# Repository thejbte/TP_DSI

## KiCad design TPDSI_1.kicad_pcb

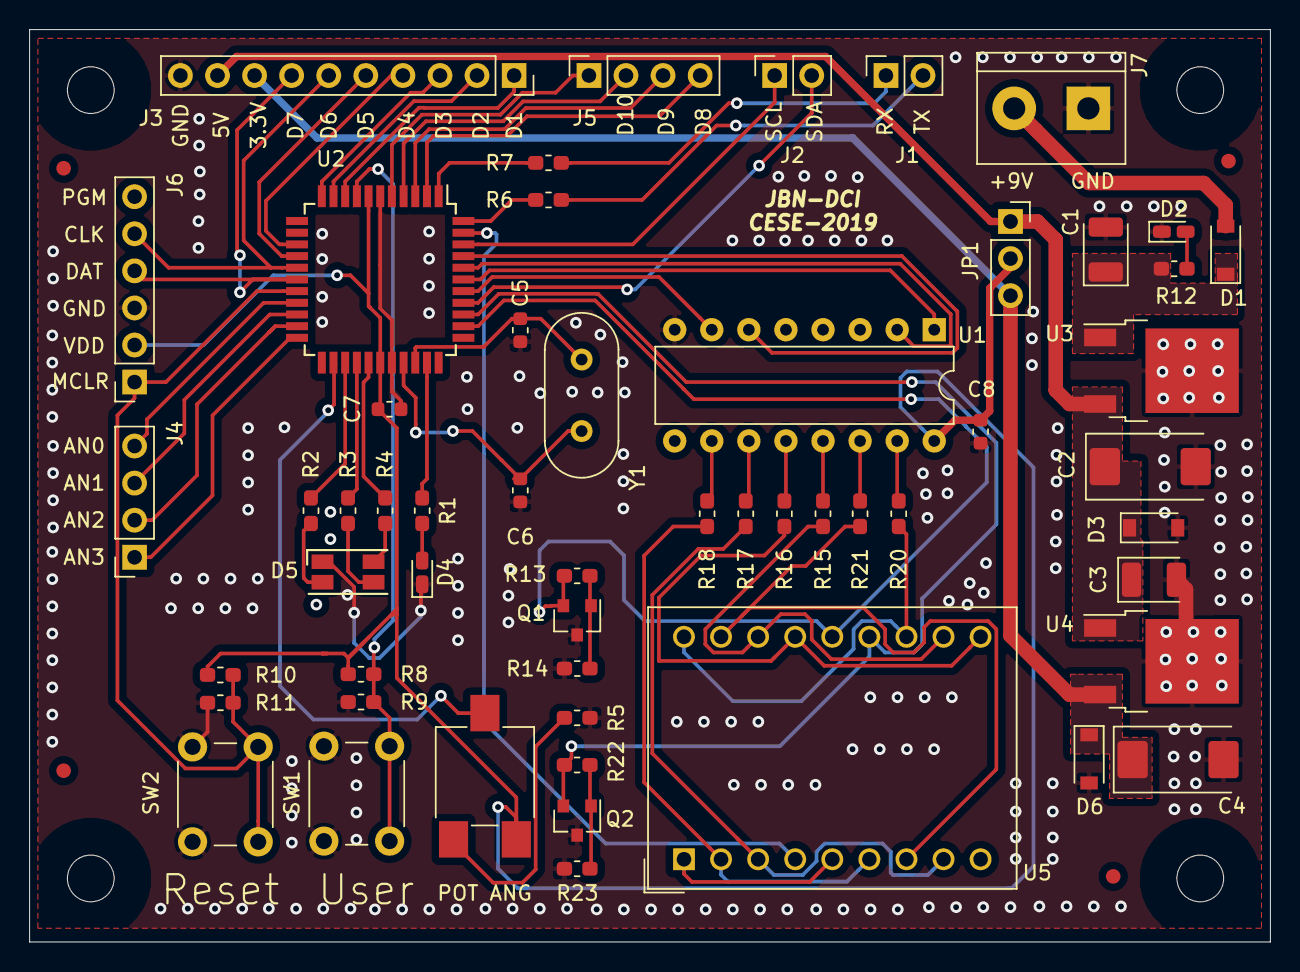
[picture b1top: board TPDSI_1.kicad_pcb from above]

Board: 2 copper layers, 85.0 x 62.5 mm, 63 parts (0 on the bottom side), 64 nets.

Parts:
C1, C3: 1uF; CP_EIA-3528-21_Kemet-B
C2: 22uF; CP_EIA-7343-20_Kemet-V
C4: 10uF; CP_EIA-7343-20_Kemet-V
C5, C6: 22pF; C_0603_1608Metric
C7, C8: 0.1uF; C_0603_1608Metric
D1: 1n4148; D_SOD-123
D2, D4: LED; LED_0603_1608Metric_Castellated
D3: D_TVS_DESD5V0S1BA-7DITR-ND; D_SOD-123
D5: LED_CRGB; LED_RGB_1210
D6: D_TVS_3V3; D_SOD-123
FID1, FID2, FID3, FID4: Fiducial; Fiducial_1mm_Mask2mm
H1, H2, H3, H4: MountingHole; MountingHole_3.2mm_M3
J1, J2: Conn_01x02_Male; PinSocket_1x02_P2.54mm_Vertical
J3: Conn_01x10_Male; PinSocket_1x10_P2.54mm_Vertical
J4, J5: Conn_01x04_Male; PinSocket_1x04_P2.54mm_Vertical
J6: Conn_01x06_Male; PinSocket_1x06_P2.54mm_Vertical
J7: Screw_Terminal_01x02; TerminalBlock_bornier-2_P5.08mm
JP1: Jumper_NC_Dual; PinSocket_1x03_P2.54mm_Vertical
Q1, Q2: Q_NPN_BCE; SOT-23
R1, R2, R3, R4, R12, R15, R16, R17, R18, R20, R21: 330; R_0603_1608Metric_Pad1.05x0.95mm_HandSolder
R5, R13, R22: 1K; R_0603_1608Metric_Pad1.05x0.95mm_HandSolder
R6, R7: 470; R_0603_1608Metric_Pad1.05x0.95mm_HandSolder
R8, R10, R14, R23: 10K; R_0603_1608Metric_Pad1.05x0.95mm_HandSolder
R9, R11: DNP-10K; R_0603_1608Metric_Pad1.05x0.95mm_HandSolder
RV1: 10K; Potentiometer_ACP_CA6-VSMD_Vertical
SW1, SW2: SW_Push; SW_PUSH_6mm_H5mm
U1: 74LS47; DIP-16_W7.62mm
U2: PIC16F1939-IPT; TQFP-44_10x10mm_P0.8mm
U3: MC7805_TO252-3(DPACK); TO-252-2
U4: TLV2217_TO252-3; TO-252-2
U5: DA56-11GWA; DA56-11CGKWA
Y1: Crystal; Crystal_HC18-U_Vertical

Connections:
+3V3: C4.1, D6.1, J3.8, JP1.3, U4.3
+5V: C2.1, C3.1, D3.1, J3.9, JP1.1, U3.3, U4.1
/9V0: D1.2, J7.2
/AN0: J4.4, U2.19
/AN1: J4.3, U2.20
/AN2: J4.2, U2.21
/AN3: J4.1, U2.22
/Display/DIG1_CA: Q1.2, R13.2, U2.35, U5.14
/Display/DIG2_CA: Q2.2, R22.2, U2.36, U5.13
/Display/DP1: U2.43, U5.4
/Display/a: R15.1, U5.11, U5.16
/Display/b: R16.1, U5.10, U5.15
/Display/c: R17.1, U5.3, U5.8
/Display/d: R18.1, U5.2, U5.6
/Display/e: U5.1, U5.5
/Display/f: R20.1, U5.12, U5.18
/Display/g: R21.1, U5.7, U5.17
/LED_B: R4.1, U2.27
/LED_G: R3.1, U2.26
/LED_OUT: R1.1, U2.32
/LED_R: R2.1, U2.25
/Microcontroller/MCLR_VPP: J6.1, R10.2, R11.1, SW2.2, U2.18
/Microcontroller/RD0: U1.7, U2.38
/Microcontroller/RD1: U1.1, U2.39
/Microcontroller/RD2: U1.2, U2.40
/Microcontroller/RD3: U1.6, U2.41
/Microcontroller/RX: J1.1, R7.2
/Microcontroller/TX: J1.2, R6.2
/Microcontroller/USER_BUTTON: R8.2, R9.1, SW1.2, U2.8
/POTENCIOMETRO: RV1.2, U2.24
/RB1: J3.1, U2.9
/RB2: J3.2, U2.10
/RB3: J3.3, U2.11
/RB4: J3.4, U2.14
/RB5: J3.5, U2.15
/RB6: J3.6, J6.5, U2.16
/RB7: J3.7, J6.4, U2.17
/RD4: J5.4, U2.2
/RD5: J5.3, U2.3
/RD6: J5.2, U2.4
/RD7: J5.1, U2.5
/SCL: J2.1, U2.42
/SDA: J2.2, U2.37
GND: C1.2, C2.2, C3.2, C4.2, C5.1, C6.1, C7.1, C8.1, D2.1, D3.2, D4.1, D5.1, D6.2, J3.10, J6.3, J7.1, Q1.3, Q2.3, R5.2, R9.2, R11.2, R14.2, R23.2, SW1.1, SW2.1, U1.8, U2.6, U2.29, U3.2, U4.2
unnamed: C1.1, D1.1, R12.1, U3.1
unnamed: C5.2, U2.31, Y1.2
unnamed: C6.2, U2.30, Y1.1
unnamed: D2.2, R12.2
unnamed: D4.2, R1.2
unnamed: D5.2, R2.2
unnamed: D5.3, R3.2
unnamed: D5.4, R4.2
unnamed: Q1.1, R13.1, R14.1
unnamed: Q2.1, R22.1, R23.1
unnamed: R5.1, RV1.3
unnamed: R6.1, U2.44
unnamed: R7.1, U2.1
unnamed: R15.2, U1.13
unnamed: R16.2, U1.12
unnamed: R17.2, U1.11
unnamed: R18.2, U1.10
unnamed: R20.2, U1.15
unnamed: R21.2, U1.14
VDD: C7.2, C8.2, J6.2, JP1.2, R8.1, R10.1, RV1.1, U1.16, U2.7, U2.28

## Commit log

2019-05-06 Diseño Tp DSI Rev 1.0
2019-05-07 Se agrega bus a jerarquia y pines de programación icsp
2019-05-14 Se Organiza conexiones de alimentacion con elementos de la biblioteca power, se quitan algunas etiquetas y se coloca la fuente en hoja principal
2019-05-15 Se agregan recomendaciones izq->dcha (In/Out), se Reorganiza jerarquía y bus de datos, se coloca graphics lines para indicar submodulos
2019-05-15 Se Corre Reglas 0 Errores. 2 Warnings
2019-06-04 Se agrega ubicación de componentes, asociación de footprint, pendiente Ruteo.
2019-06-04 Se reorganiza componenentes lineas mas limpias y analógicas mas cerca,Se cambia potenciometro y bornera de alimentación, se colocan perforaciones en la tarjeta
2019-06-04 Se agrega recomendaciones de jacobo salvador
2019-06-05 Se agrega pdf
2019-06-10 Se agrega info del circuito,prolijidad en conexiones se corrije,ERC Warninsg no errores,pendinete Datasheet y algunos numeros de parte,Comentario esquematico1: no es necesario con los labels que esta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
2019-06-12 Se agrega reglas de pcb , se corrige ERC en sch, se agrega grilla 0.127(5 mils) , se agrega plano de tierra, keep out para perforaciones, se agrega rotulo , se rutea pocas pistas
2019-06-19 Se agrega plano gnd y ruteo de fuente con plano en vdd
2019-06-19 se comienza ruteo
2019-06-20 Se agregan ruteo de nuevas pistas
2019-06-21 se modifican pistas display
2019-06-26 Se agrega terminación de ruteo, con poligono de vcc y planos en top y bottom de gnd, pendiente realizar vías entre planos gnd, agregar datasheet y numeros de parte , insertar 3modelos 3D faltantes
2019-06-26 Se agregan modelos 3D . Stp
2019-06-27 PCB: Se agrega via stitching entre planos, Rev estable
2019-06-28 Se agregan cosas obligatorias por norma y algunas sugerencias por el docente
2019-06-28 se agrega serigrafía a conectores, pin header, industria colombiana
2019-06-29 TP Finalizado
